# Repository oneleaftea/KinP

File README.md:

# RP2040 Pico Mod for the Kinesis Advantage Keyboard

This project includes the PCB design and the QMK default files for replacing a Kinesis Advantage/Contoured keyboard with a Raspberry Pi RP2040 Pico MCU.

## Attribution

Credit goes to Michael Stapelberg for the original KinT PCB as well as Ming-Gih Lam for developing several key changes:
 * Michael Stapelberg's [KinT project](https://github.com/kinx-project/kint) ([blog](https://michael.stapelberg.ch/posts/2020-07-09-kint-kinesis-keyboard-controller/))
 * Ming-Gih Lam's [pillzmod project](https://github.com/dcpedit/pillzmod)

The pillzmod version was especially useful in a few key changes. I borrowed the following:
 * Changing the KinT's usage of SMD LED's and resistors to use through-hole components.
 * Moving the main keywell FFC/FPC connectors and utilizing a combo footprint to be useable on later Advantage series (KB500 and KB600 variants utilizing the FFC cables) as well as older (Classic and Essential) Contoured series that connect directly to the board. 

## Note on MCU

I have built several of these boards using cheaper RP2040 MCU's from Tenstar Robot on Aliexpress, mainly due to the cheaper price as well as the USB-C connector. The pinout is the same as the official Raspberry Pi Pico, but as I have never used one, I can only vouch for it working with the Aliexpress ones (which are also available on Amazon). Just to be safe, I did not use GP23 and GP29, which are the two GPIO pins that are available on the Tenstar Robot version but not available on the official Raspberry Pi Pico.

Here is the pinout of the Tenstar Robot version:

Here is the pinout of the official version:

## Note on the Firmware

The default QMK configuration and keymap is a standard QWERTY layout, and includes all 4 LED's. The keypad LED is linked to the `keypad` button on the F-row, and corresponds to the second layer. The `program` button only works on this second layer to avoid accidentally programming the keyboard. Once you are on the second layer, simply press the `program` keyboard, and you will be able to flash your uf2 file.

## Note on the PCB

I have exported the PCB gerber files according to JLCPCB's recommended settings and have ordered and tested the files. The included zip file should work just fine for ordering, but feel free to check out the KiCAD files and generate your own gerber files. 

## Parts List

### Components

| Position | Description | Qty | Notes |
| -------- | ----------- | --- | ----- |
| J1-J4    | Molex 39-53-2135 | 2 - 6  | [Link](https://octopart.com/39-53-2135-molex-7670149?r=sp)
| J3-J4    | Molex 39-53-2134 | 0 - 2  | Contoured only, [Link](https://octopart.com/search?q=Molex+39-53-2134)
| U1       | Header pins (1x20) | 2 | Should come with dev board
| D1-D4    | 3.0mm LED | 4 | [Amazon](https://a.co/d/3NseNQ2)
| R1-R4    | various resistors | 4 | Affects brightness

Additional notes: The pillzmod version used 1.8mm LED's, but the 3mm ones fit as well. Since I used different color LED's, I used different resistors each. After testing with a 3.3V supply, this worked for me:
 * Pink LED: 1K resistor
 * Green LED: 3.9K resistor
 * Blue LED: 2.2K resistor
 * Light Green LED: 100 Ohm resistor

Please see the [KinT](https://github.com/kinx-project/kint) and [pillzmod](https://github.com/dcpedit/pillzmod) projects for more details on parts and ideas for cable management. 

## Images of Final Build

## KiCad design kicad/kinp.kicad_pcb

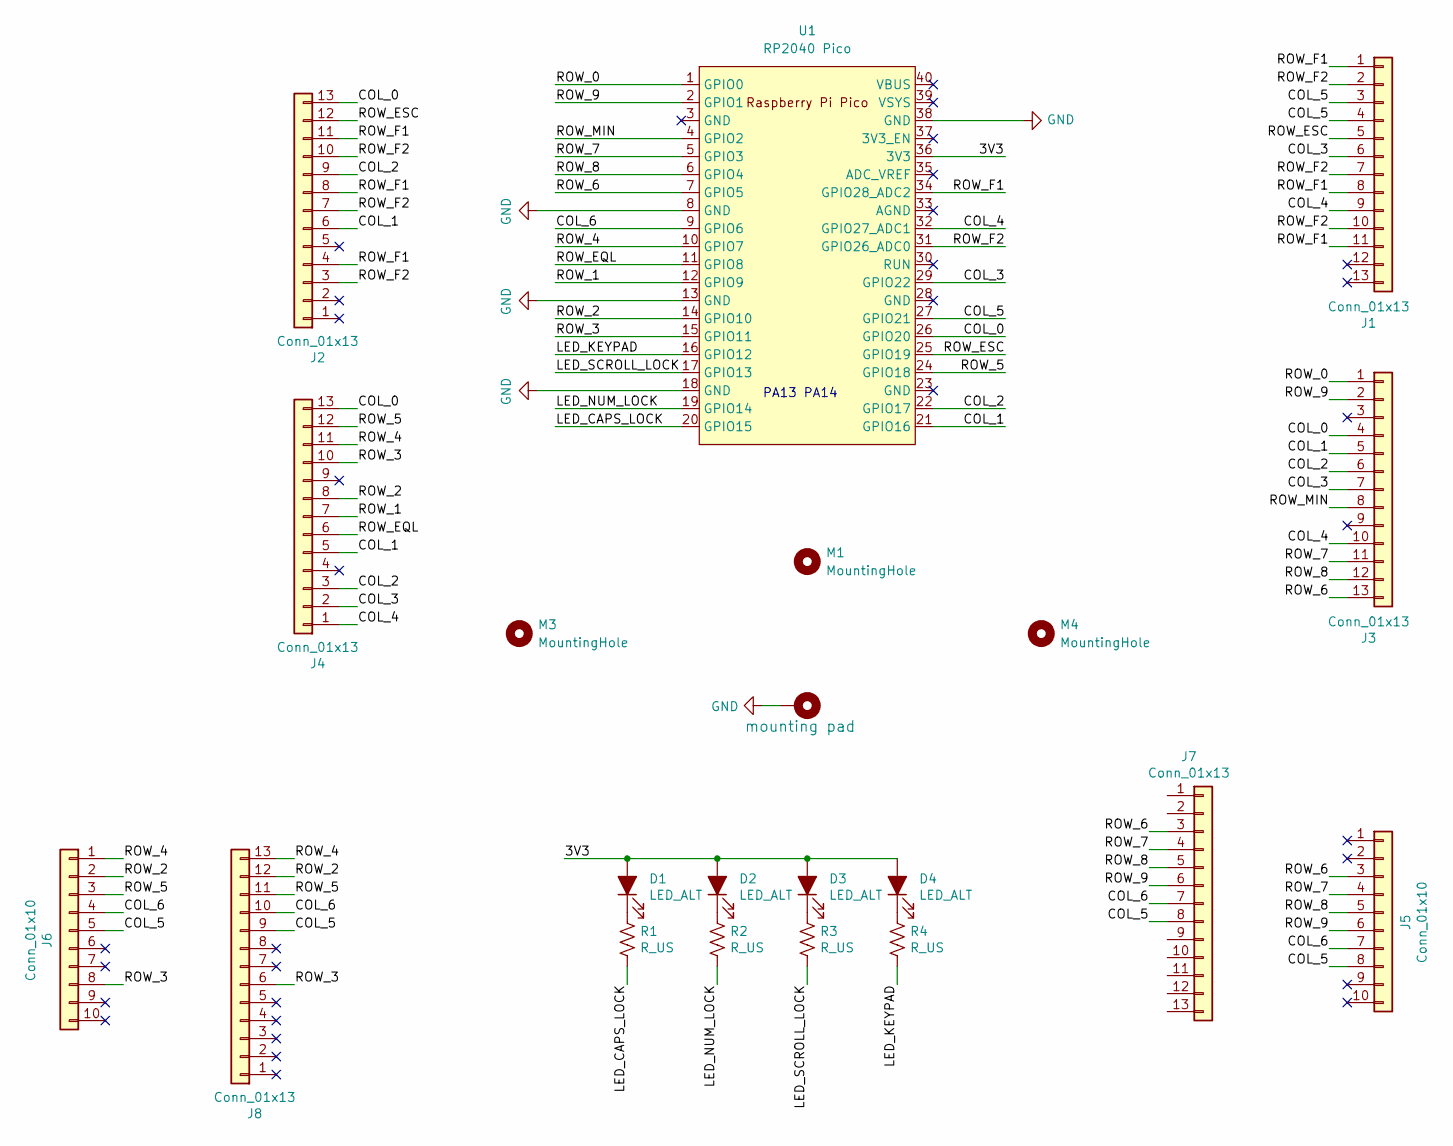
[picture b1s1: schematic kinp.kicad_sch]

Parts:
D1, D2, D3, D4: LED_ALT; LED_D3.0mm
H1: mounting pad; MountingHole_4.3mm_M4_Pad
J1, J2: Conn_01x13; Molex_0039532135
J3, J4: Conn_01x13; Molex_039532134
J5, J6: Conn_01x10; Pin_Header_Straight_1x10_Pitch2.54mm
J7, J8: Conn_01x13; Molex_039532135_Squished
M1: MountingHole; Kinesis_Locating_6.5mm
M3, M4: MountingHole; Kinesis_Notch
R1, R2, R3, R4: R_US; R_Axial_DIN0204_L3.6mm_D1.6mm_P5.08mm_Horizontal
U1: RP2040 Pico; RPi_Pico_TH

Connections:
/3V3: D1.2 (A), D2.2 (A), D3.2 (A), D4.2 (A), U1.36 (3V3)
/COL_0: J2.13, J3.4, J4.13, U1.26 (GPIO20)
/COL_1: J2.6, J3.5, J4.5, U1.21 (GPIO16)
/COL_2: J2.9, J3.6, J4.3, U1.22 (GPIO17)
/COL_3: J1.6, J3.7, J4.2, U1.29 (GPIO22)
/COL_4: J1.9, J3.10, J4.1, U1.32 (GPIO27_ADC1)
/COL_5: J1.3, J1.4, J5.8, J6.5, J7.8, J8.9, U1.27 (GPIO21)
/COL_6: J5.7, J6.4, J7.7, J8.10, U1.9 (GPIO6)
/LED_CAPS_LOCK: R1.2, U1.20 (GPIO15)
/LED_KEYPAD: R4.2, U1.16 (GPIO12)
/LED_NUM_LOCK: R2.2, U1.19 (GPIO14)
/LED_SCROLL_LOCK: R3.2, U1.17 (GPIO13)
/ROW_0: J3.1, U1.1 (GPIO0)
/ROW_1: J4.7, U1.12 (GPIO9)
/ROW_2: J4.8, J6.2, J8.12, U1.14 (GPIO10)
/ROW_3: J4.10, J6.8, J8.6, U1.15 (GPIO11)
/ROW_4: J4.11, J6.1, J8.13, U1.10 (GPIO7)
/ROW_5: J4.12, J6.3, J8.11, U1.24 (GPIO18)
/ROW_6: J3.13, J5.3, J7.3, U1.7 (GPIO5)
/ROW_7: J3.11, J5.4, J7.4, U1.5 (GPIO3)
/ROW_8: J3.12, J5.5, J7.5, U1.6 (GPIO4)
/ROW_9: J3.2, J5.6, J7.6, U1.2 (GPIO1)
/ROW_EQL: J4.6, U1.11 (GPIO8)
/ROW_ESC: J1.5, J2.12, U1.25 (GPIO19)
/ROW_F1: J1.1, J1.8, J1.11, J2.4, J2.8, J2.11, U1.34 (GPIO28_ADC2)
/ROW_F2: J1.2, J1.7, J1.10, J2.3, J2.7, J2.10, U1.31 (GPIO26_ADC0)
/ROW_MIN: J3.8, U1.4 (GPIO2)
GND: H1.1, U1.8 (GND), U1.13 (GND), U1.18 (GND), U1.38 (GND)
unnamed: D1.1 (K), R1.1
unnamed: D2.1 (K), R2.1
unnamed: D3.1 (K), R3.1
unnamed: D4.1 (K), R4.1

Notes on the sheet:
PA13 PA14

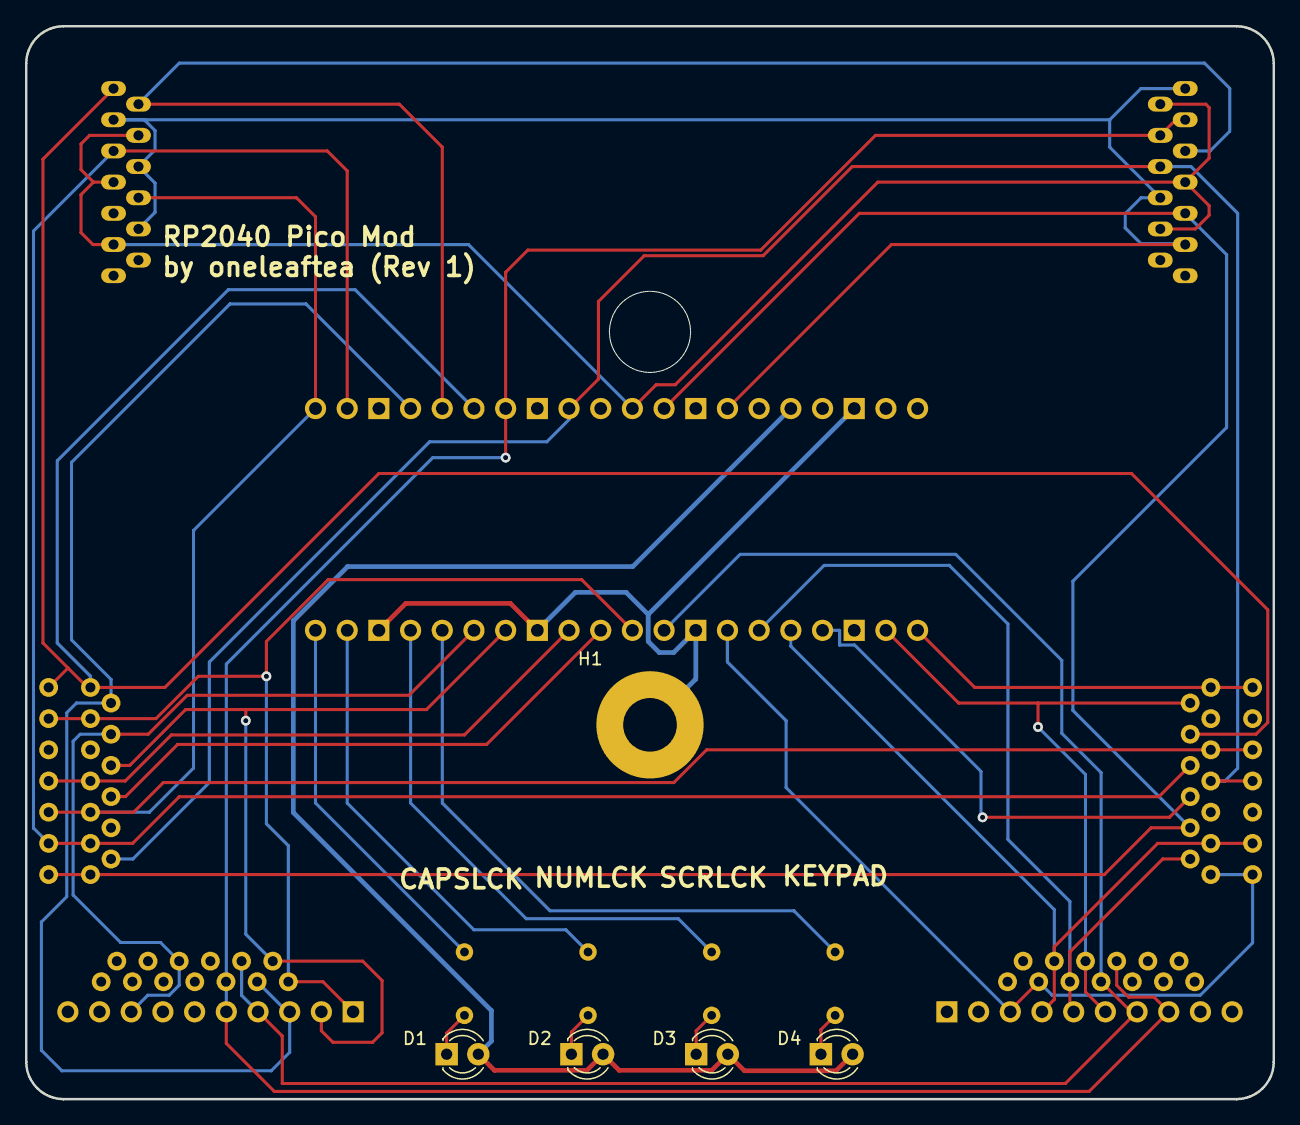
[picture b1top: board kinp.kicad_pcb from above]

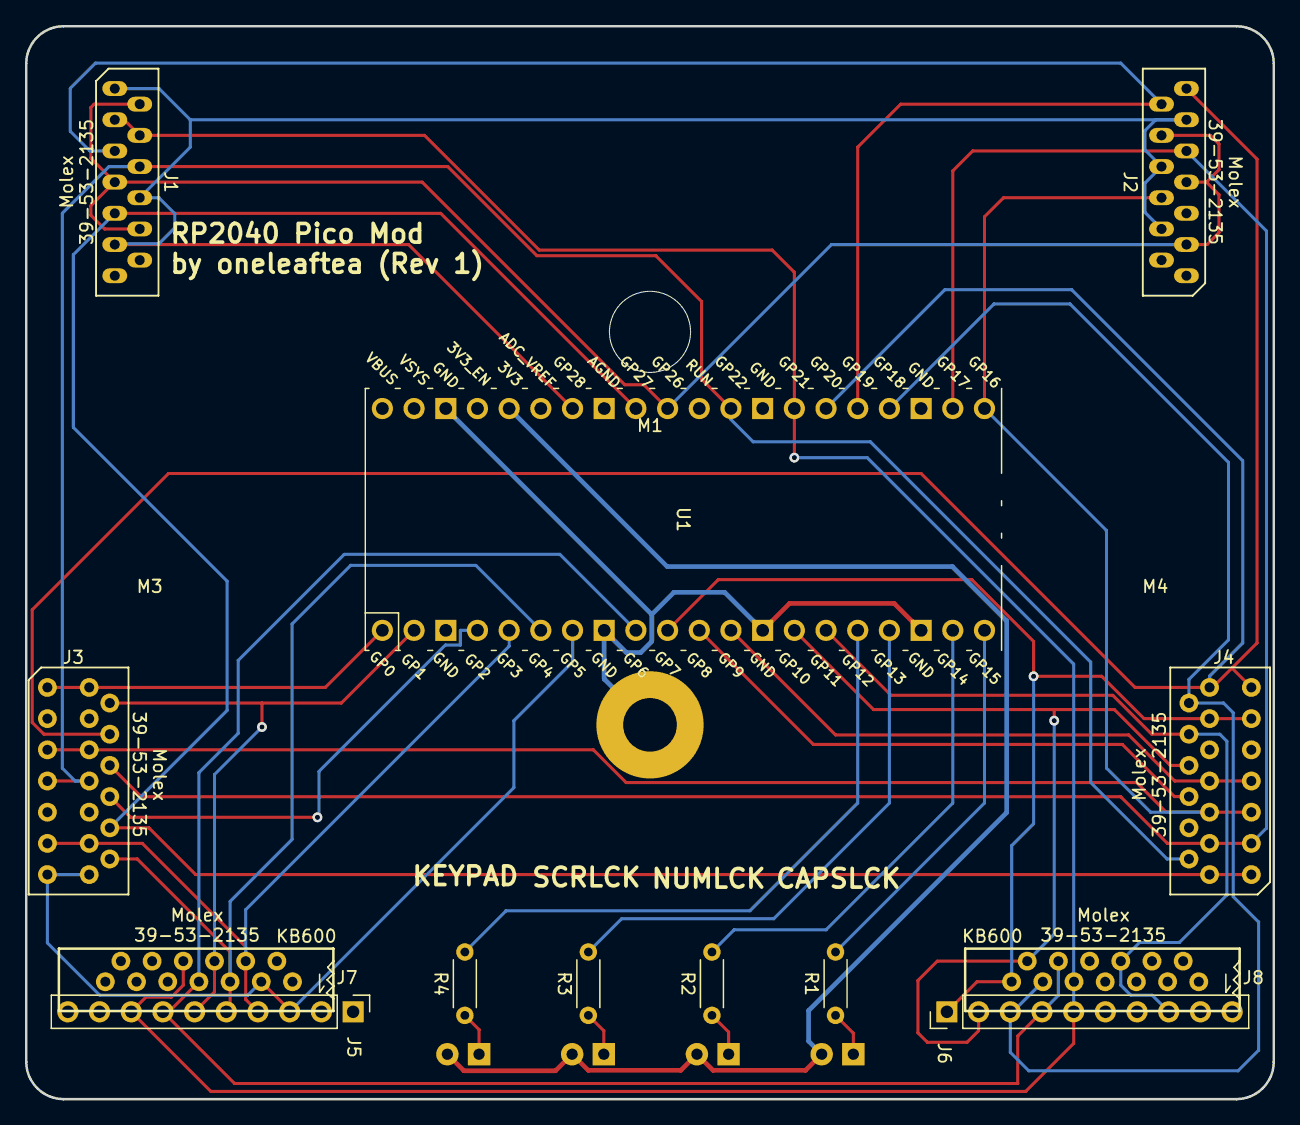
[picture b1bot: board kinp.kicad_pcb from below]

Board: 2 copper layers, 100.0 x 86.0 mm, 21 parts (16 on the bottom side), 32 nets.

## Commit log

2025-04-25 README
2025-04-25 More images and README work
2025-04-25 README parts list added
2025-04-25 Tweaks
2025-04-25 More README stuff
2025-04-25 Firmware fix
